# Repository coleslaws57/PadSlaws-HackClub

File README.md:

# PadSlaws-HackClub
My real attempt at making/designing a hackpad

PadSlaws
My PadSlaws is a 4 key macropad with a rotary encoder, an OLED Display, has 4 LEDs under each bey, and uses QMK firmware.

Features:
Dual layer plastic case with an extra acrylic piece to protect the inside.
128x32 OLED Display.
EC11 Rotary encoder.
4 RGB LEDs.
4 Keys.

CAD Model: Made in Fusion360.

Everything fits together using 4 M3 Bolts that hold it all together.

It has 3 separate printed pieces. The base where the PCB sits, and the top cover and one acrylic plate. One to cover the electronics, so that you can see all the cool stuff on the inside.

Schematic

PCB:
Here's my PCB! It was made in KiCad.

PCB Schematic

Firmware Overview:
This hackpad uses QMK firmware for everything.

Right now all the keys just do basic stuff (typing letters), but its pretty easy to change that.

BOM:
Here should be everything you need to make this hackpad

1xSeeed Studio XIAO RP2040
4xCherry MX compatible switches
4x1u keycaps
4xSK6812MINI-E RGB LEDs
1xEC11 rotary encoder with push switch
1xEncoder knob
1x0.91" I2C OLED display
1x1x04 2.54mm pin header for OLED
1xCustom PCB
1x3D printed top case
1x3D printed bottom case
4xBolts
4xHeat-set inserts or nuts

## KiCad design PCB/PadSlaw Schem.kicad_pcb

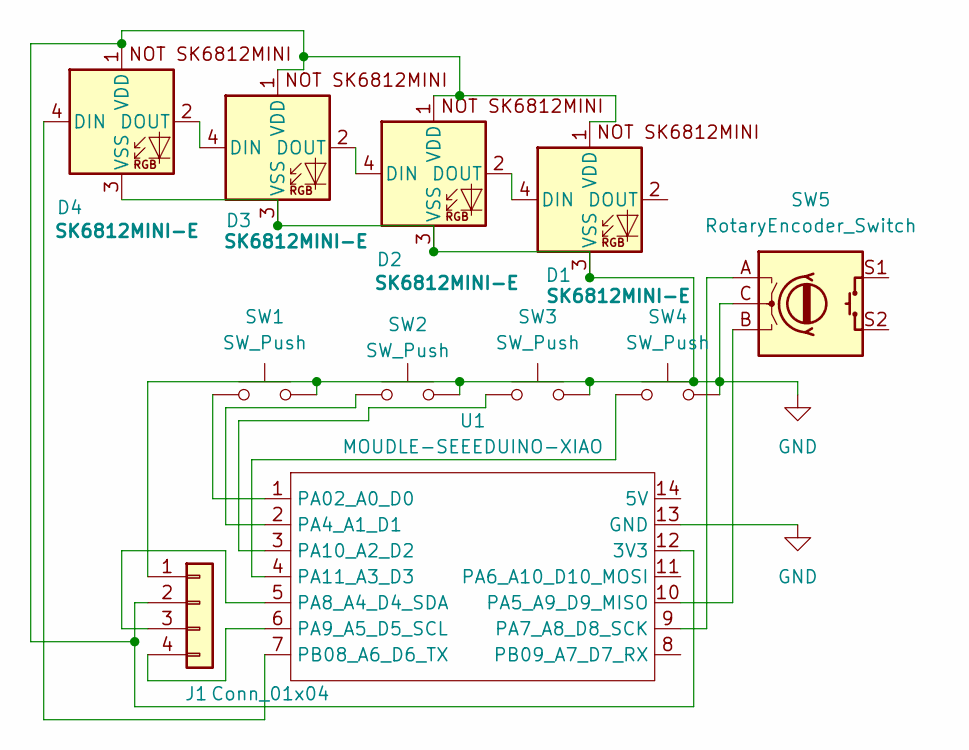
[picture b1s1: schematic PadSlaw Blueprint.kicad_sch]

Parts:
D1, D2, D3, D4: SK6812MINI-E; LED-APA102-2020
J1: Conn_01x04; PinHeader_1x04_P2.54mm_Vertical
SW1, SW2, SW3, SW4: SW_Push; SW_Cherry_MX_1.00u_PCB
SW5: RotaryEncoder_Switch; RotaryEncoder_Alps_EC11E-Switch_Vertical_H20mm
U1: MOUDLE-SEEEDUINO-XIAO; XIAO-Generic-Hybrid-14P-2.54-21X17.8MM

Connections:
GND: D1.3 (VSS), D2.3 (VSS), D3.3 (VSS), D4.3 (VSS), J1.1, SW1.2, SW2.2, SW3.2, SW4.2, SW5.C, U1.13 (GND)
unnamed: D1.4 (DIN), D2.2 (DOUT)
unnamed: D1.1 (VDD), D2.1 (VDD), D3.1 (VDD), D4.1 (VDD), J1.2, U1.12 (3V3)
unnamed: D2.4 (DIN), D3.2 (DOUT)
unnamed: D3.4 (DIN), D4.2 (DOUT)
unnamed: D4.4 (DIN), U1.7 (PB08_A6_D6_TX)
unnamed: J1.3, U1.5 (PA8_A4_D4_SDA)
unnamed: J1.4, U1.6 (PA9_A5_D5_SCL)
unnamed: SW1.1, U1.1 (PA02_A0_D0)
unnamed: SW2.1, U1.2 (PA4_A1_D1)
unnamed: SW5.B, U1.10 (PA5_A9_D9_MISO)
unnamed: SW5.A, U1.9 (PA7_A8_D8_SCK)
unnamed: SW3.1, U1.3 (PA10_A2_D2)
unnamed: SW4.1, U1.4 (PA11_A3_D3)

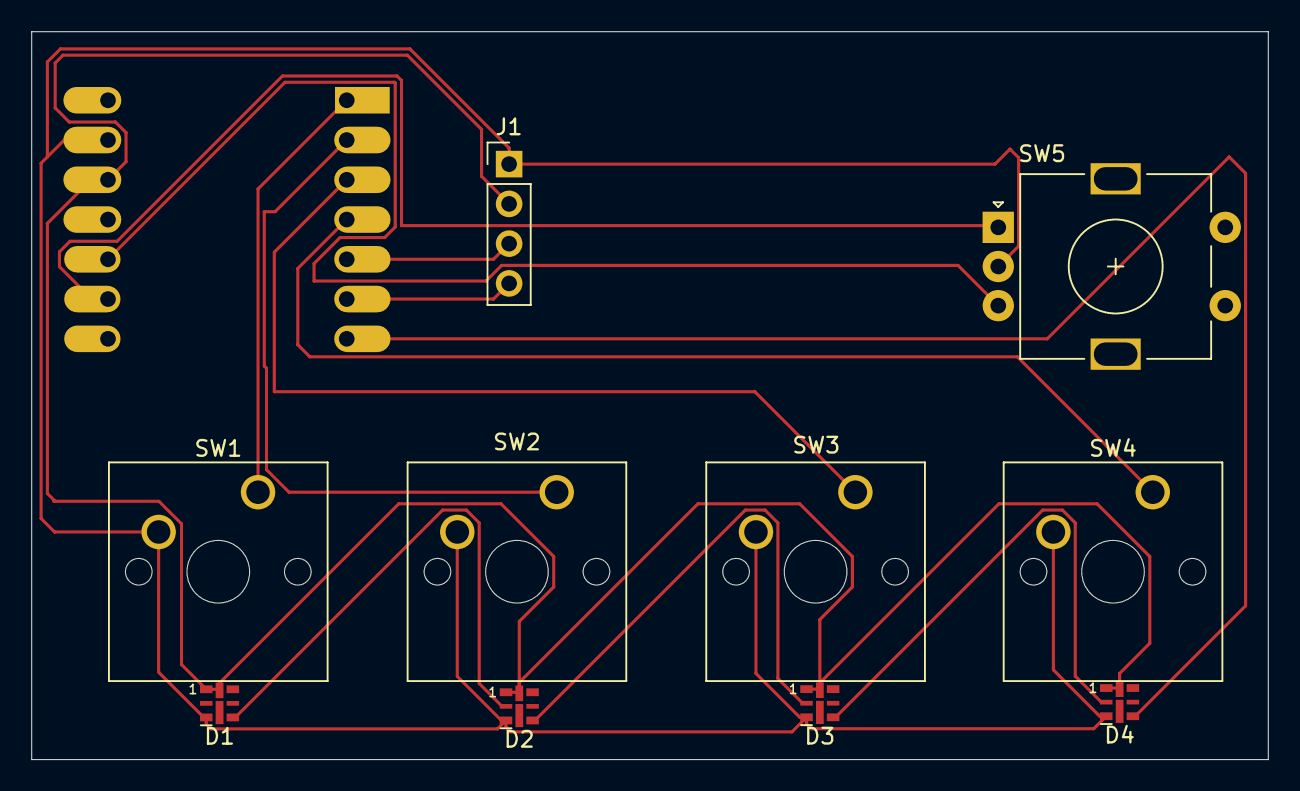
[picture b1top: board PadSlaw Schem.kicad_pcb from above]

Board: 2 copper layers, 79.0 x 46.5 mm, 11 parts (1 on the bottom side), 14 nets.

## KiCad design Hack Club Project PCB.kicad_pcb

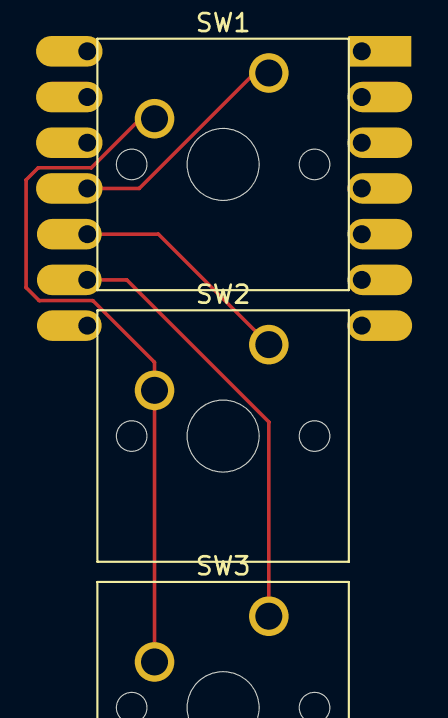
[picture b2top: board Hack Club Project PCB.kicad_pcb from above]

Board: 2 copper layers, 4 parts (1 on the bottom side), 4 nets.

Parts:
SW1, SW2, SW3: SW_Push; SW_Cherry_MX_1.00u_PCB
U1: MOUDLE-SEEEDUINO-XIAO; XIAO-Generic-Hybrid-14P-2.54-21X17.8MM

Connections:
GND: SW1.2, SW2.2, SW3.2, U1.13 (GND)
unnamed: SW2.1, U1.10 (PA5_A9_D9_MISO)
unnamed: SW1.1, U1.11 (PA6_A10_D10_MOSI)
unnamed: SW3.1, U1.9 (PA7_A8_D8_SCK)

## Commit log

2026-06-03 Rename Hack Club Project PCB-B_Cu.gbr to PCB/Hack Club Project PCB-B_Cu.gbr
2026-06-03 Rename Hack Club Project PCB-B_Mask.gbr to PCB/Hack Club Project PCB-B_Mask.gbr
2026-06-03 Rename Hack Club Project PCB-B_Paste.gbr to PCB/Hack Club Project PCB-B_Paste.gbr
2026-06-03 Rename Hack Club Project PCB-B_Silkscreen.gbr to PCB/Hack Club Project PCB-B_Silkscreen.gbr
2026-06-03 Rename Hack Club Project PCB-Edge_Cuts.gbr to PCB/Hack Club Project PCB-Edge_Cuts.gbr
2026-06-03 Rename Hack Club Project PCB-F_Cu.gbr to PCB/Hack Club Project PCB-F_Cu.gbr
2026-06-03 Rename Hack Club Project PCB-F_Mask.gbr to PCB/Hack Club Project PCB-F_Mask.gbr
2026-06-03 Rename Hack Club Project PCB-F_Paste.gbr to PCB/Hack Club Project PCB-F_Paste.gbr
2026-06-03 Rename rules.mk to Firmware/rules.mk
2026-06-03 Rename keymap.c to Firmware/keymap.c
2026-06-03 Rename keyboard.json to Firmware/keyboard.json
2026-06-03 Rename config.h to Firmware/config.h
2026-06-03 Rename readme.md to Firmware/readme.md
2026-06-03 Rename PadSlaws.step to CAD/PadSlaws.step
2026-06-03 Rename PadSlaw pro.kicad_sch to PCB/PadSlaw pro.kicad_sch
2026-06-03 Rename PadSlaw pro.kicad_pro to PCB/PadSlaw pro.kicad_pro
2026-06-03 Rename PadSlaw pro.kicad_prl to PCB/PadSlaw pro.kicad_prl
2026-06-03 Rename PadSlaw Blueprint.kicad_sch to PCB/PadSlaw Blueprint.kicad_sch
2026-06-03 Rename PadSlaw Schem.kicad_pcb to PCB/PadSlaw Schem.kicad_pcb
2026-06-03 Rename Hack Club Project PCB-F_Silkscreen.gbr to PCB/Hack Club Project PCB-F_Silkscreen.gbr
2026-06-03 Rename Hack Club Project PCB-NPTH.drl to PCB/Hack Club Project PCB-NPTH.drl
2026-06-03 Rename Hack Club Project PCB-PTH.drl to PCB/Hack Club Project PCB-PTH.drl
2026-06-03 Rename Hack Club Project PCB-job.gbrjob to PCB/Hack Club Project PCB-job.gbrjob
2026-06-03 Rename Hack Club Project PCB.kicad_pcb to PCB/Hack Club Project PCB.kicad_pcb
2026-06-03 Rename PadSlaw Schem.kicad_pro to PCB/PadSlaw Schem.kicad_pro
2026-06-03 Rename PadSlaw pro.kicad_pcb to PCB/PadSlaw pro.kicad_pcb
